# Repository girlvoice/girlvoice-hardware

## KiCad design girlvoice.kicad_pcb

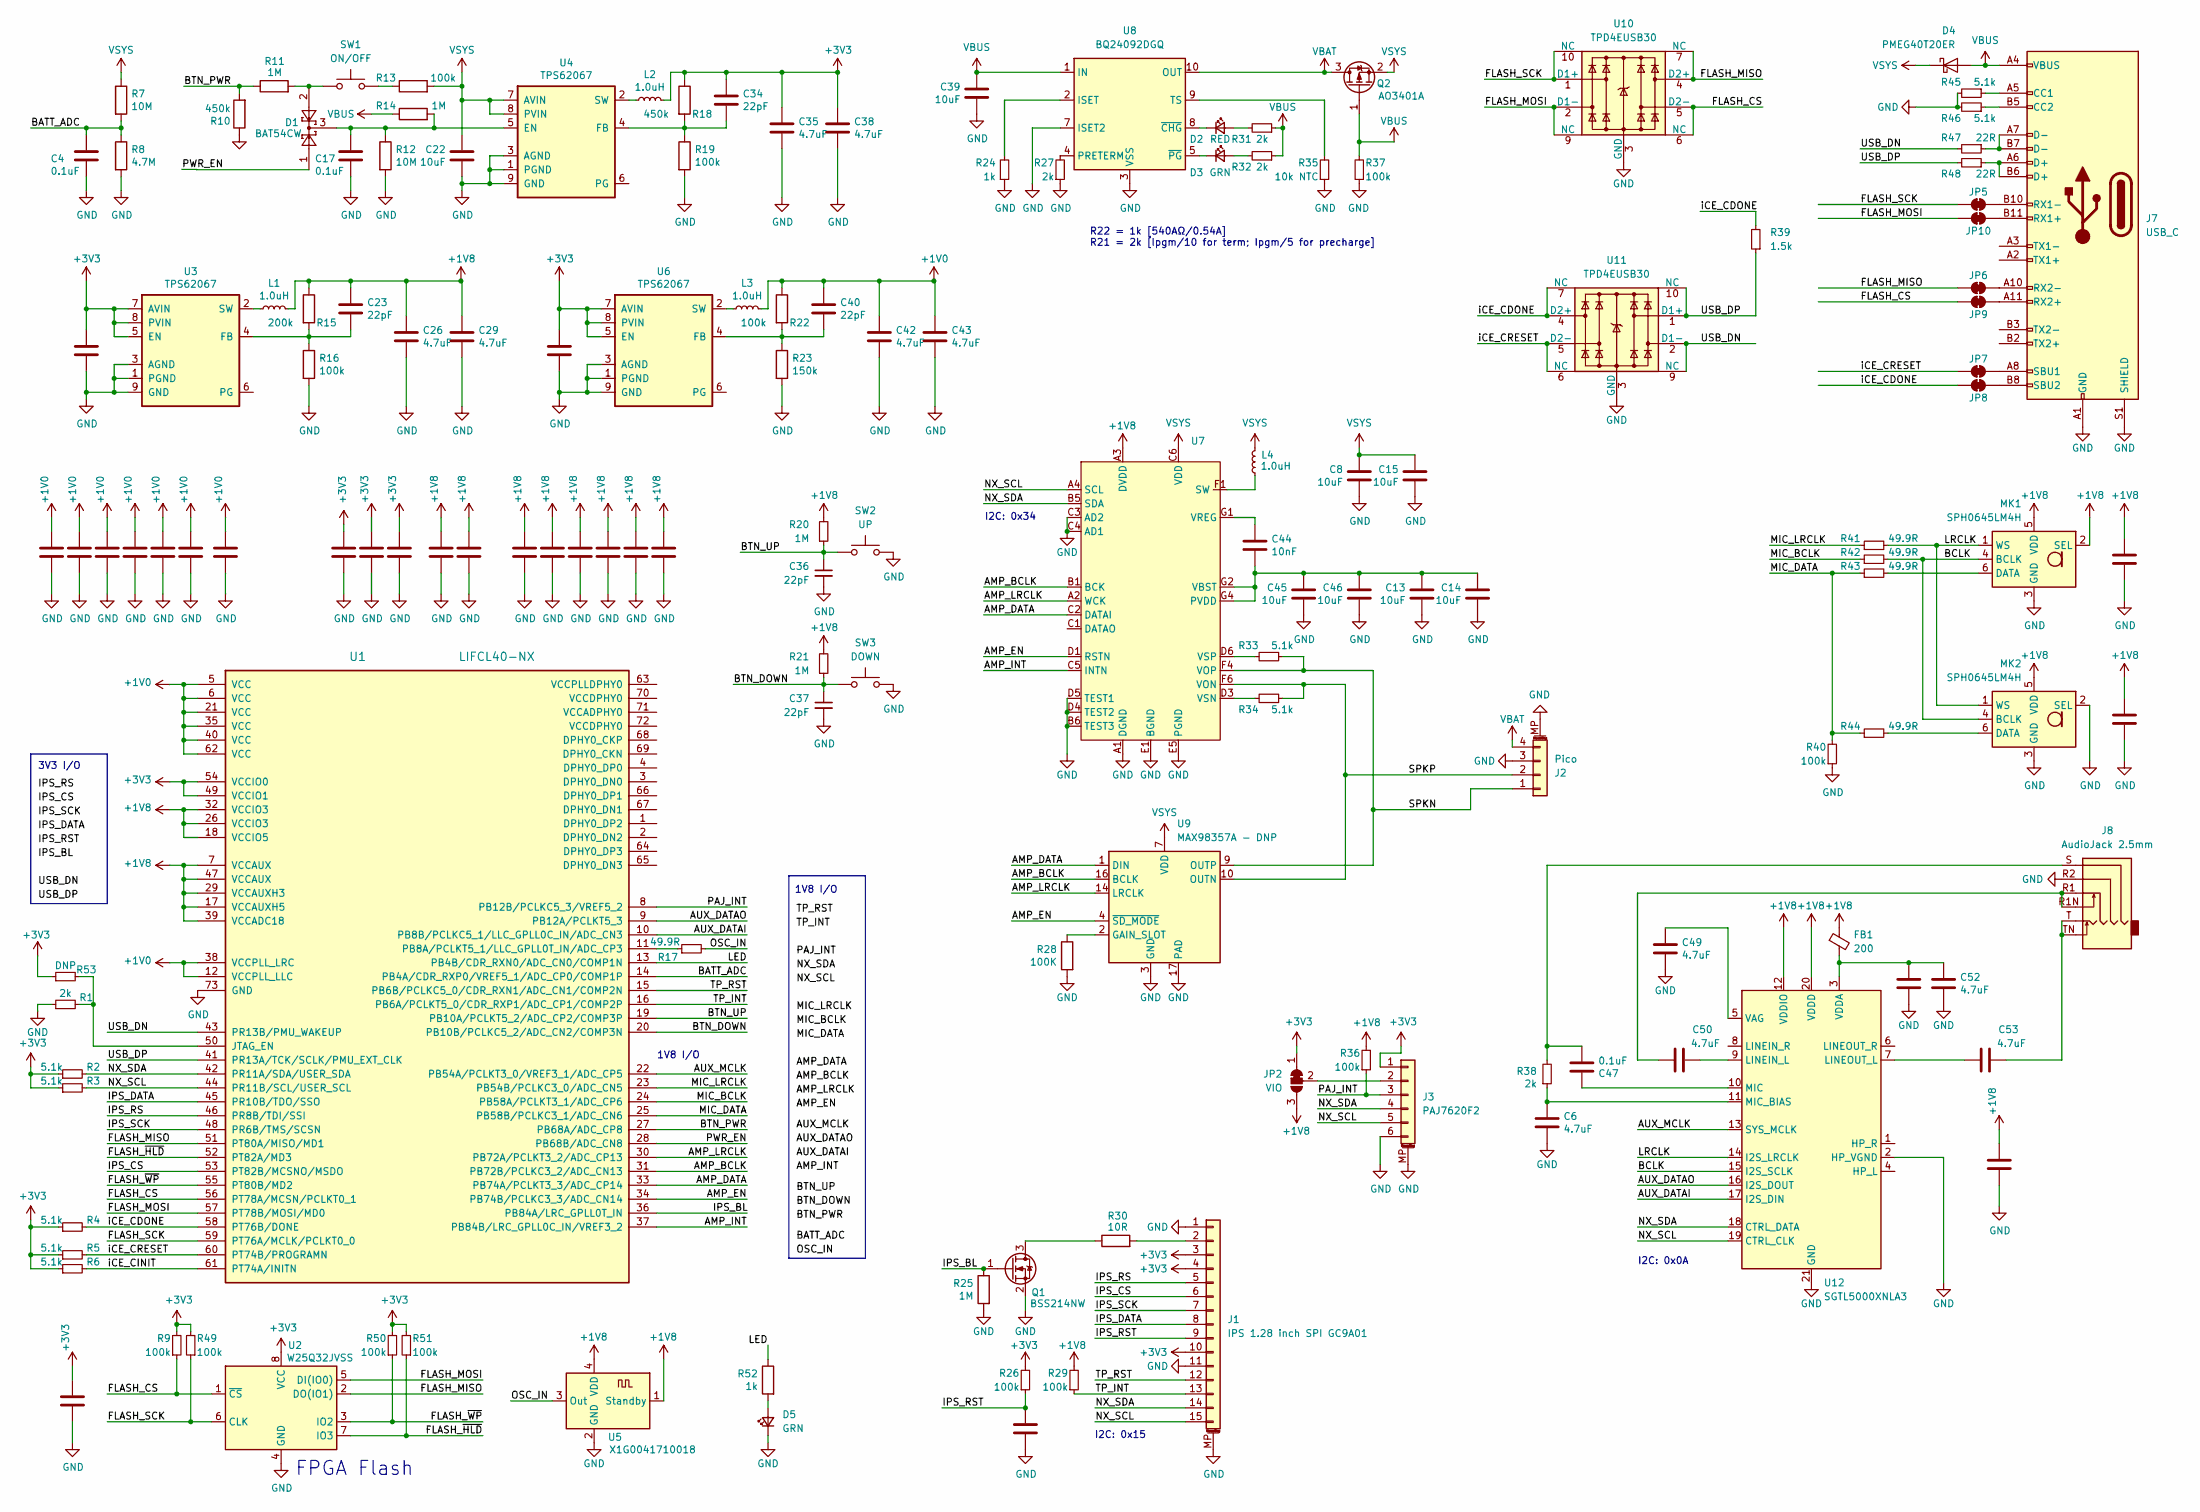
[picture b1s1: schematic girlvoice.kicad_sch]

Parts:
C1, C2, C4, C5, C7, C9, C10, C11, C16, C17, C18, C19, C20, C21, C24, C25, C27, C28, C30, C31, C32, C41, C47, C51, C54, C55: 0.1uF; C_0402_1005Metric
C3, C6, C26, C29, C35, C38, C42, C43, C49, C50, C52, C53: 4.7uF; C_0805_2012Metric
C8, C12, C13, C14, C15, C22, C33, C39, C45, C46: 10uF; C_0805_2012Metric
C23, C34, C36, C37, C40: 22pF; C_0402_1005Metric
C44: 10nF; C_0402_1005Metric
D1: BAT54CW; SOT-323_SC-70
D2: RED; LED_0603_1608Metric
D3, D5: GRN; LED_0603_1608Metric
D4: PMEG40T20ER; Nexperia_CFP3_SOD-123W
FB1: 200; L_0603_1608Metric
J1: IPS 1.28 inch SPI GC9A01; TE_1-1734839-5_1x15-1MP_P0.5mm_Horizontal
J2: Pico; Molex_PicoBlade_53261-0471_1x04-1MP_P1.25mm_Horizontal
J3: PAJ7620F2; TE_0-1734839-6_1x06-1MP_P0.5mm_Horizontal
J7: USB_C; USB_C_Receptacle_Molex_105450-0101
J8: AudioJack 2.5mm; Jack_3.5mm_PJ31060-I_Horizontal
JP2: VIO; SolderJumper-3_P1.3mm_Bridged12_RoundedPad1.0x1.5mm
JP5, JP6, JP7, JP8, JP9, JP10: SolderJumper_2_Bridged; SolderJumper-2_P1.3mm_Bridged_RoundedPad1.0x1.5mm
L1, L2, L3: 1.0uH; L_0805_2012Metric
L4: 1.0uH; L_Bourns-SRN4018
MK1, MK2: SPH0645LM4H; Knowles_SPH0645LM4H-6_3.5x2.65mm
Q1: BSS214NW; SOT-323_SC-70
Q2: AO3401A; SOT-23
R1, R27, R31, R32, R38: 2k; R_0402_1005Metric
R2, R3, R4, R5, R6, R33, R34, R45, R46: 5.1k; R_0402_1005Metric
R7, R12: 10M; R_0402_1005Metric
R8: 4.7M; R_0402_1005Metric
R9, R13, R16, R19, R22, R26, R29, R36, R37, R40, R49, R50, R51: 100k; R_0402_1005Metric
R10, R18: 450k; R_0402_1005Metric
R11, R14, R20, R21, R25: 1M; R_0402_1005Metric
R15: 200k; R_0402_1005Metric
R17, R41, R42, R43, R44: 49.9R; R_0402_1005Metric
R23: 150k; R_0402_1005Metric
R24, R52: 1k; R_0402_1005Metric
R28: 100K; R_0402_1005Metric
R30: 10R; R_0402_1005Metric
R35: 10k NTC; R_0603_1608Metric
R39: 1.5k; R_0402_1005Metric
R47, R48: 22R; R_0402_1005Metric
R53: DNP; R_0402_1005Metric
SW1: ON/OFF; SW_SPST_CK_KMS2xxGP
SW2: UP; SW_SPST_CK_KMS2xxGP
SW3: DOWN; SW_SPST_CK_KMS2xxGP
U1: LIFCL40-NX; QFN-72-1EP_10x10mm_P0.5mm_EP6x6mm
U2: W25Q32JVSS; WSON-8-1EP_6x5mm_P1.27mm_EP3.4x4mm
U3, U6: TPS62067; WSON-8-1EP_2x2mm_P0.5mm_EP0.9x1.6mm_ThermalVias
U4: TPS62067; WSON-8-1EP_6x5mm_P1.27mm_EP3.4x4mm
U5: X1G0041710018; Oscillator_SMD_Abracon_ASDMB-4Pin_2.5x2.0mm
U7: NXP_VFBGA-42_2.6x3mm_Layout6x7_P0.4mm_Ball0.25mm_Pad0.24mm
U8: BQ24092DGQ; HVSSOP-10-1EP_3x3mm_P0.5mm_EP1.57x1.88mm_ThermalVias
U9: MAX98357A - DNP; TQFN-16-1EP_3x3mm_P0.5mm_EP1.23x1.23mm
U10, U11: TPD4EUSB30; USON-10_2.5x1.0mm_P0.5mm
U12: SGTL5000XNLA3; QFN-20-1EP_3x3mm_P0.4mm_EP1.65x1.65mm

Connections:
+1V0: C1.1, C2.1, C5.1, C7.1, C9.1, C10.1, C11.1, C40.1, C42.1, C43.1, L3.2, R22.1, U1.5 (VCC), U1.6 (VCC), U1.12 (VCCPLL_LLC), U1.21 (VCC), U1.35 (VCC), U1.38 (VCCPLL_LRC), U1.40 (VCC), U1.62 (VCC)
+1V8: C20.1, C21.1, C23.1, C24.1, C25.1, C26.1, C27.1, C28.1, C29.1, C30.1, C31.1, C32.1, C54.1, C55.1, FB1.1, JP2.3 (B), L1.2, MK1.2 (SEL), MK1.5 (VDD), MK2.5 (VDD), R15.1, R20.2, R21.2, R29.2, R36.2, U1.7 (VCCAUX), U1.17 (VCCAUXH5), U1.18 (VCCIO5), U1.26 (VCCIO3), U1.29 (VCCAUXH3), U1.32 (VCCIO3), U1.39 (VCCADC18), U1.47 (VCCAUX), U5.1 (Standby), U5.4 (VDD), U7.A3 (DVDD), U7.B3 (DVDD), U12.12 (VDDIO), U12.20 (VDDD)
+3V3: C3.1, C12.1, C16.1, C18.1, C19.1, C33.1, C34.1, C35.1, C38.1, J1.3, J1.4, J1.10, J3.1, JP2.1 (A), L2.2, R2.1, R3.1, R4.1, R5.1, R6.1, R9.2, R18.1, R26.2, R49.2, R50.2, R51.2, R53.1, U1.49 (VCCIO1), U1.54 (VCCIO0), U2.8 (VCC), U3.5 (EN), U3.7 (AVIN), U3.8 (PVIN), U6.5 (EN), U6.7 (AVIN), U6.8 (PVIN)
/AMP_BCLK: U1.31 (PB72B/PCLKC3_2/ADC_CN13), U7.B1 (BCK), U9.16 (BCLK)
/AMP_DATA: U1.33 (PB74A/PCLKT3_3/ADC_CP14), U7.C2 (DATAI), U9.1 (DIN)
/AMP_EN: U1.34 (PB74B/PCLKC3_3/ADC_CN14), U7.D1 (RSTN), U9.4 (~SD_MODE)
/AMP_INT: U1.37 (PB84B/LRC_GPLL0C_IN/VREF3_2), U7.C5 (INTN)
/AMP_LRCLK: U1.30 (PB72A/PCLKT3_2/ADC_CP13), U7.A2 (WCK), U7.B2 (WCK), U9.14 (LRCLK)
/AUX_DATAI: U1.10 (PB8B/PCLKC5_1/LLC_GPLL0C_IN/ADC_CN3), U12.17 (I2S_DIN)
/AUX_DATAO: U1.9 (PB12A/PCLKT5_3), U12.16 (I2S_DOUT)
/AUX_MCLK: U1.22 (PB54A/PCLKT3_0/VREF3_1/ADC_CP5), U12.13 (SYS_MCLK)
/BATT_ADC: C4.1, R7.2, R8.1, U1.14 (PB4A/CDR_RXP0/VREF5_1/ADC_CP0/COMP1P)
/BCLK: MK1.4 (BCLK), MK2.4 (BCLK), R42.2, U12.15 (I2S_SCLK)
/BTN_DOWN: C37.1, R21.1, SW3.1, U1.20 (PB10B/PCLKC5_2/ADC_CN2/COMP3N)
/BTN_PWR: R10.2, R11.1, U1.27 (PB68A/ADC_CP8)
/BTN_UP: C36.1, R20.1, SW2.1, U1.19 (PB10A/PCLKT5_2/ADC_CP2/COMP3P)
/FLASH_CS: JP9.1 (A), R9.1, U1.56 (PT78A/MCSN/PCLKT0_1), U2.1 (~CS), U10.5 (D2-), U10.6 (NC)
/FLASH_MISO: JP6.1 (A), U1.51 (PT80A/MISO/MD1), U2.2 (DO(IO1)), U10.4 (D2+), U10.7 (NC)
/FLASH_MOSI: JP10.1 (A), U1.57 (PT78B/MOSI/MD0), U2.5 (DI(IO0)), U10.2 (D1-), U10.9 (NC)
/FLASH_SCK: JP5.1 (A), R49.1, U1.59 (PT76A/MCLK/PCLKT0_0), U2.6 (CLK), U10.1 (D1+), U10.10 (NC)
/FLASH_~HLD: R51.1, U1.52 (PT82A/MD3), U2.7 (IO3)
/FLASH_~WP: R50.1, U1.55 (PT80B/MD2), U2.3 (IO2)
/IPS_BL: Q1.1 (G), R25.1, U1.36 (PB84A/LRC_GPLL0T_IN)
/IPS_CS: J1.6, U1.53 (PT82B/MCSNO/MSDO)
/IPS_DATA: J1.8, U1.45 (PR10B/TDO/SSO)
/IPS_RS: J1.5, U1.46 (PR8B/TDI/SSI)
/IPS_RST: C41.1, J1.9, R26.1
/IPS_SCK: J1.7, U1.48 (PR6B/TMS/SCSN)
/LED: R52.1, U1.13 (PB4B/CDR_RXN0/ADC_CN0/COMP1N)
/LRCLK: MK1.1 (WS), MK2.1 (WS), R41.2, U12.14 (I2S_LRCLK)
/MIC_BCLK: R42.1, U1.24 (PB58A/PCLKT3_1/ADC_CP6)
/MIC_DATA: R40.2, R43.1, R44.1, U1.25 (PB58B/PCLKC3_1/ADC_CN6)
/MIC_LRCLK: R41.1, U1.23 (PB54B/PCLKC3_0/ADC_CN5)
/NX_SCL: J1.15, J3.5, R3.2, U1.44 (PR11B/SCL/USER_SCL), U7.A4 (SCL), U7.B4 (SCL), U12.19 (CTRL_CLK)
/NX_SDA: J1.14, J3.4, R2.2, U1.42 (PR11A/SDA/USER_SDA), U7.B5 (SDA), U12.18 (CTRL_DATA)
/OSC_IN: R17.2, U5.3 (Out)
/PAJ_INT: J3.3, R36.1, U1.8 (PB12B/PCLKC5_3/VREF5_2)
/PWR_EN: D1.1, U1.28 (PB68B/ADC_CN8)
/SPKN: J2.1, R33.1, U7.F4 (VOP), U9.9 (OUTP)
/SPKP: J2.2, R34.1, U7.F6 (VON), U9.10 (OUTN)
/TP_INT: J1.13, R29.1, U1.16 (PB6A/PCLKT5_0/CDR_RXP1/ADC_CP1/COMP2P)
/TP_RST: J1.12, U1.15 (PB6B/PCLKC5_0/CDR_RXN1/ADC_CN1/COMP2N)
/USB_DN: R47.2, U1.43 (PR13B/PMU_WAKEUP), U11.2 (D1-), U11.9 (NC)
/USB_DP: R39.1, R48.2, U1.41 (PR13A/TCK/SCLK/PMU_EXT_CLK), U11.1 (D1+), U11.10 (NC)
/iCE_CDONE: JP8.1 (A), R4.2, R39.2, U1.58 (PT76B/DONE), U11.4 (D2+), U11.7 (NC)
/iCE_CINIT: R6.2, U1.61 (PT74A/INITN)
/iCE_CRESET: JP7.1 (A), R5.2, U1.60 (PT74B/PROGRAMN), U11.5 (D2-), U11.6 (NC)
GND: C1.2, C2.2, C3.2, C4.2, C5.2, C6.2, C7.2, C8.2, C9.2, C10.2, C11.2, C12.2, C13.2, C14.2, C15.2, C16.2, C17.2, C18.2, C19.2, C20.2, C21.2, C22.2, C24.2, C25.2, C26.2, C27.2, C28.2, C29.2, C30.2, C31.2, C32.2, C33.2, C35.2, C36.2, C37.2, C38.2, C39.2, C41.2, C42.2, C43.2, C45.2, C46.2, C49.2, C51.2, C52.2, C54.2, C55.2, D5.1 (K), J1.1, J1.11, J1.MP (MountPin), J2.3, J2.MP (MountPin), J3.6, J3.MP (MountPin), J7.A1 (GND), J7.A12 (GND), J7.B1 (GND), J7.B12 (GND), J7.S1 (SHIELD), J8.R2, MK1.3 (GND), MK2.2 (SEL), MK2.3 (GND), Q1.2 (S), R1.1, R8.2, R10.1, R12.2, R16.2, R19.2, R23.2, R24.1, R25.2, R27.1, R28.2, R35.1, R37.1, R40.1, R45.2, R46.2, SW1.SH, SW2.2, SW2.SH, SW3.2, SW3.SH, U1.73 (GND), U2.4 (GND), U3.1 (PGND), U3.3 (AGND), U3.9 (GND), U4.1 (PGND), U4.3 (AGND), U4.9 (GND), U5.2 (GND), U6.1 (PGND), U6.3 (AGND), U6.9 (GND), U7.A1 (DGND), U7.A5 (DGND), U7.A6 (DGND), U7.B6 (TEST3), U7.C3 (AD2), U7.C4 (AD1), U7.D2 (DGND), U7.D4 (TEST2), U7.D5 (TEST1), U7.E1 (BGND), U7.E2 (BGND), U7.E3 (BGND), U7.E4 (DGND), U7.E5 (PGND), U7.E6 (DGND), U7.F5 (PGND), U8.3 (VSS), U8.7 (ISET2), U8.11 (VSS), U9.3 (GND), U9.11 (GND), U9.15 (GND), U9.17 (PAD), U10.3 (GND), U10.8 (GND), U11.3 (GND), U11.8 (GND), U12.2 (HP_VGND), U12.21 (GND)
unnamed: C13.1, C14.1, C44.2, C45.1, C46.1, U7.G2 (VBST), U7.G3 (VBST), U7.G4 (PVDD), U7.G5 (PVDD), U7.G6 (PVDD)
unnamed: C47.2, J8.S, R38.2
unnamed: C50.1, J8.R1, J8.R1N
unnamed: C53.2, J8.T, J8.TN
unnamed: D1.2, R11.2, SW1.1
unnamed: D2.2 (A), R31.2
unnamed: D2.1 (K), U8.8 (~CHG)
unnamed: D3.2 (A), R32.2
unnamed: D3.1 (K), U8.5 (~PG)
unnamed: D5.2 (A), R52.2
unnamed: J1.2, R30.2
unnamed: J3.2, JP2.2 (C)
unnamed: J7.A5 (CC1), R45.1
unnamed: J7.B5 (CC2), R46.1
unnamed: J7.A6 (D+), J7.B6 (D+), R48.1
unnamed: J7.A7 (D-), J7.B7 (D-), R47.1
unnamed: J7.B11 (RX1+), JP10.2 (B)
unnamed: J7.B10 (RX1-), JP5.2 (B)
unnamed: J7.A11 (RX2+), JP9.2 (B)
unnamed: J7.A10 (RX2-), JP6.2 (B)
unnamed: J7.A8 (SBU1), JP7.2 (B)
unnamed: J7.B8 (SBU2), JP8.2 (B)
unnamed: L4.1, U7.F1 (SW), U7.F2 (SW), U7.F3 (SW)
unnamed: MK1.6 (DATA), R43.2
unnamed: MK2.6 (DATA), R44.2
unnamed: Q1.3 (D), R30.1
unnamed: R13.1, SW1.2
unnamed: R1.2, R53.2, U1.50 (JTAG_EN)
unnamed: R17.1, U1.11 (PB8A/PCLKT5_1/LLC_GPLL0T_IN/ADC_CP3)
unnamed: C23.2, R15.2, R16.1, U3.4 (FB)
unnamed: L1.1, U3.2 (SW)
unnamed: C17.1, D1.3, R12.1, R14.2, U4.5 (EN)
unnamed: C34.2, R18.2, R19.1, U4.4 (FB)
unnamed: L2.1, U4.2 (SW)
unnamed: C40.2, R22.2, R23.1, U6.4 (FB)
unnamed: L3.1, U6.2 (SW)
unnamed: C44.1, U7.G1 (VREG)
unnamed: R34.2, U7.D3 (VSN)
unnamed: R33.2, U7.D6 (VSP)
unnamed: R24.2, U8.2 (ISET)
unnamed: R27.2, U8.4 (PRETERM)
unnamed: R35.2, U8.9 (TS)
unnamed: R28.1, U9.2 (GAIN_SLOT)
unnamed: C50.2, U12.9 (LINEIN_L)
unnamed: C53.1, U12.7 (LINEOUT_L)
unnamed: C47.1, U12.10 (MIC)
unnamed: C6.1, R38.1, U12.11 (MIC_BIAS)
unnamed: C49.1, U12.5 (VAG)
unnamed: C51.1, C52.1, FB1.2, U12.3 (VDDA)
VBAT: J2.4, Q2.3 (D), U8.10 (OUT)
VBUS: C39.1, D4.2 (A), J7.A4 (VBUS), J7.A9 (VBUS), J7.B4 (VBUS), J7.B9 (VBUS), Q2.1 (G), R14.1, R31.1, R32.1, R37.2, U8.1 (IN)
VSYS: C8.1, C15.1, C22.1, D4.1 (K), L4.2, Q2.2 (S), R7.1, R13.2, U4.7 (AVIN), U4.8 (PVIN), U7.C6 (VDD), U9.7 (VDD), U9.8 (VDD)

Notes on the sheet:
I2C: 0x15
I2C: 0x34
1V8 I/O
R22 = 1k [540AΩ/0.54A] R21 = 2k [Ipgm/10 for term; Ipgm/5 for precharge]
FPGA Flash
I2C: 0x0A
3V3 I/O

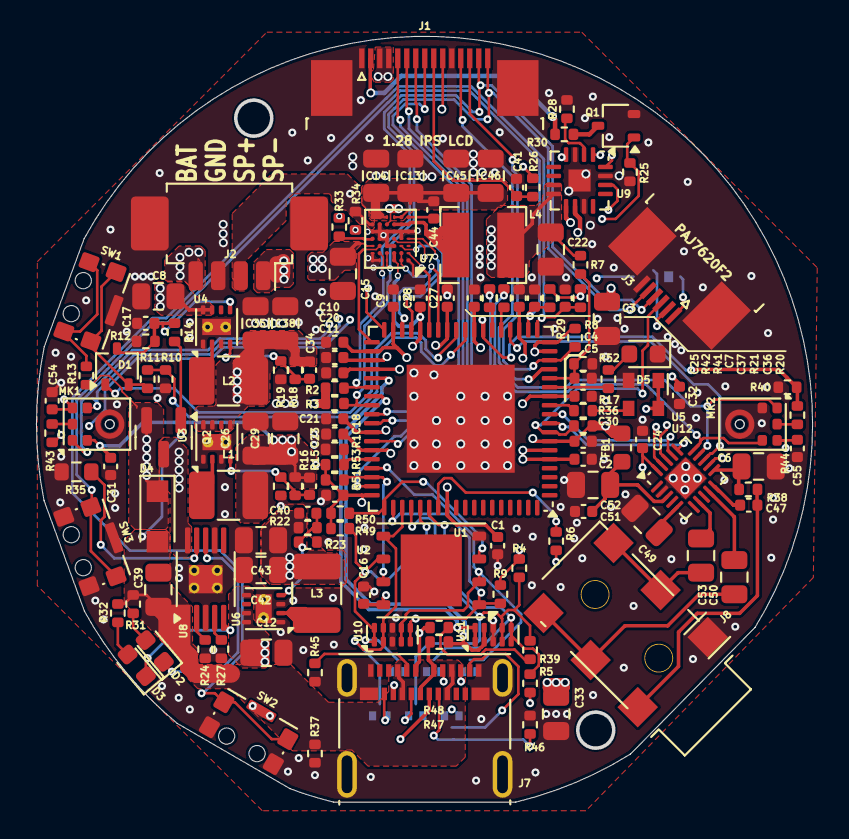
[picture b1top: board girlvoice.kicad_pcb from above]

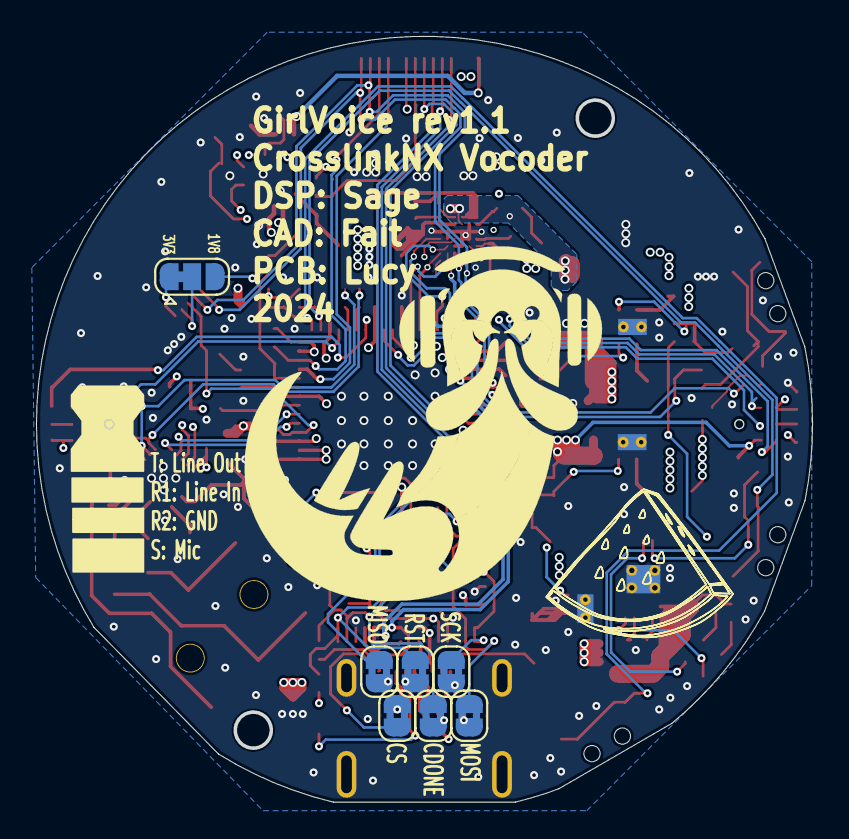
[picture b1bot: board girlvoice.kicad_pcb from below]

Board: 4 copper layers, 43.1 x 42.5 mm, 148 parts (7 on the bottom side), 100 nets.

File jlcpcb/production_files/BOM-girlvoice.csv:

Comment,Designator,Footprint,LCSC
200,FB1,L_0603_1608Metric,C1002
1k,"R24,R52",R_0402_1005Metric,C11702
BQ24092DGQ,U8,HVSSOP-10-1EP_3x3mm_P0.5mm_EP1.57x1.88mm_ThermalVias,C133237
USB_C,J7,USB_C_Receptacle_Molex_105450-0101,C134092
AO3401A,Q2,SOT-23,C15127
10nF,C44,C_0402_1005Metric,C15195
0.1uF,"C1,C10,C11,C16,C17,C18,C19,C2,C20,C21,C24,C25,C27,C28,C30,C31,C32,C4,C41,C47,C5,C51,C54,C55,C7,C9",C_0402_1005Metric,C1525
22pF,"C23,C34,C36,C37,C40",C_0402_1005Metric,C1555
10uF,"C12,C13,C14,C15,C22,C33,C39,C45,C46,C8",C_0805_2012Metric,C15850
4.7uF,"C26,C29,C3,C35,C38,C42,C43,C49,C50,C52,C53,C6",C_0805_2012Metric,C1779
BAT54CW,D1,SOT-323_SC-70,C192144
ON/OFF,"SW1,SW2,SW3",SW_SPST_CK_KMS2xxGP,C221703
RED,D2,LED_0603_1608Metric,C2286
1.0uH,"L1,L2,L3",L_1210_3225Metric_Pad1.42x2.65mm_HandSolder,C237284
10R,R30,R_0402_1005Metric,C25077
22R,"R47,R48",R_0402_1005Metric,C25092
49.9R,"R17,R41,R42,R43,R44",R_0402_1005Metric,C25120
PMEG40T20ER,D4,Nexperia_CFP3_SOD-123W,C255588
X1G0041710018,U5,Oscillator_SMD_Abracon_ASDMB-4Pin_2.5x2.0mm,C255991
100k,"R13,R16,R19,R22,R26,R28,R29,R36,R37,R40,R49,R50,R51,R9",R_0402_1005Metric,C25741
200k,R15,R_0402_1005Metric,C25764
1.5k,R39,R_0402_1005Metric,C25867
5.1k,"R2,R3,R33,R34,R4,R45,R46,R5,R6",R_0402_1005Metric,C25905
10M,"R12,R7",R_0402_1005Metric,C26082
1M,"R11,R14,R20,R21,R25",R_0402_1005Metric,C26083
SGTL5000XNLA3,U12,QFN-20-1EP_3x3mm_P0.4mm_EP1.65x1.65mm,C2651833
IPS 1.28 inch SPI GC9A01,J1,TE_1-1734839-5_1x15-1MP_P0.5mm_Horizontal,C2880769
Pico,J2,Molex_PicoBlade_53261-0471_1x04-1MP_P1.25mm_Horizontal,C2905011
1.0uH,L4,L_Bourns-SRN4018,C351087
AudioJack4_SwitchTR1,J8,Jack_2.5mm_PJ_242DSMT-I_Horizontal,C381133
450k,"R10,R18",R_0402_1005Metric,C407681
2k,"R1,R27,R31,R32,R38",R_0402_1005Metric,C4109
BSS214NW,Q1,SOT-323_SC-70,C412741
4.7M,R8,R_0402_1005Metric,C474132
~,U7,NXP_VFBGA-42_2.6x3mm_Layout6x7_P0.4mm_Ball0.25mm_Pad0.24mm,C5162561
TPD4EUSB30,"U10,U11",USON-10_2.5x1.0mm_P0.5mm,C558427
W25Q32JVSS,U2,WSON-8-1EP_6x5mm_P1.27mm_EP3.4x4mm,C571260
TPS62067,"U3,U4,U6",WSON-8-1EP_2x2mm_P0.5mm_EP0.9x1.6mm_ThermalVias,C7098
GRN,"D3,D5",LED_0603_1608Metric,C72038
10k NTC,R35,R_0603_1608Metric,C76589
150k,R23,R_0402_1005Metric,C93947
SPH0645LM4H,MK2,Knowles_SPH0645LM4H-6_3.5x2.65mm,
SPH0645LM4H,MK1,Knowles_SPH0645LM4H-6_3.5x2.65mm,
PAJ7620F2,J3,TE_0-1734839-6_1x06-1MP_P0.5mm_Horizontal,
LIFCL40-NX,U1,QFN-72-1EP_10x10mm_P0.5mm_EP6x6mm,
MAX98357A,U9,TQFN-16-1EP_3x3mm_P0.5mm_EP1.23x1.23mm,
DNP,R53,R_0402_1005Metric,

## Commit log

2024-05-06 RMV backups
2024-05-14 Add interactive HTML BOM
2024-12-08 ADD: Manufacturing files
2024-12-08 silly lucy
2024-12-08 ignore
2024-12-08 ADD: Fabrication instructions
2024-12-08 UPD: connect pushbutton shield to groundplane for better mechanical support
2025-01-14 add licence
